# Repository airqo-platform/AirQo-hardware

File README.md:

# AirQo-hardware
The AirQo air quality monitoring device is an IoT connected device that provides realtime measurement of particualate matter concentrations and environmental readings (atmospheric pressure, relative humidity and temperature). The device is powered by a Li-ion battery and connects to the internet over a 2G GSM network.
## Folder Structure
- [**Firmware**](./firmware)
    - Contains the various firmware projects for AirQo hardware, specific to different build environments.
- [**Hardware**](./hardware)
    - Contains the hardware designs for AirQo hardware, 3d models for 3d printing, Schematic and PCB designs.
- [**docs**](./docs)
    - Contains relevant documentation and templates.
## Hardware design
The device is currently designed around an [Atmega2560](https://ww1.microchip.com/downloads/aemDocuments/documents/OTH/ProductDocuments/DataSheets/ATmega640-1280-1281-2560-2561-Datasheet-DS40002211A.pdf) microcontroller, that hosts the device firmware.
### block diagram 

### Sensors
* Particulate matter sensors [Plantower Pms5003]()

* Environmental sensors     [BME280](),[SHT25]()

* GPS                        [NEO6-GPS-module]()

* Communication              [Sim800l-GSM-GPRS]()

### CAD tools
List of tools used to design the AirQo monitor
PCB tools, 3d tools, links to design files here on github

## Firmware design
### Developed with cpp and arduino framework
The firmware provides the AirQo monitor with a number of features
* Realtime measurements of particulate matter concentrations
* Logging of data to local storage
* Over The Air Firmware Updates (OTA)
## License
This project is licensed under the MIT License - see the [LICENSE.md](LICENSE.md) file for details

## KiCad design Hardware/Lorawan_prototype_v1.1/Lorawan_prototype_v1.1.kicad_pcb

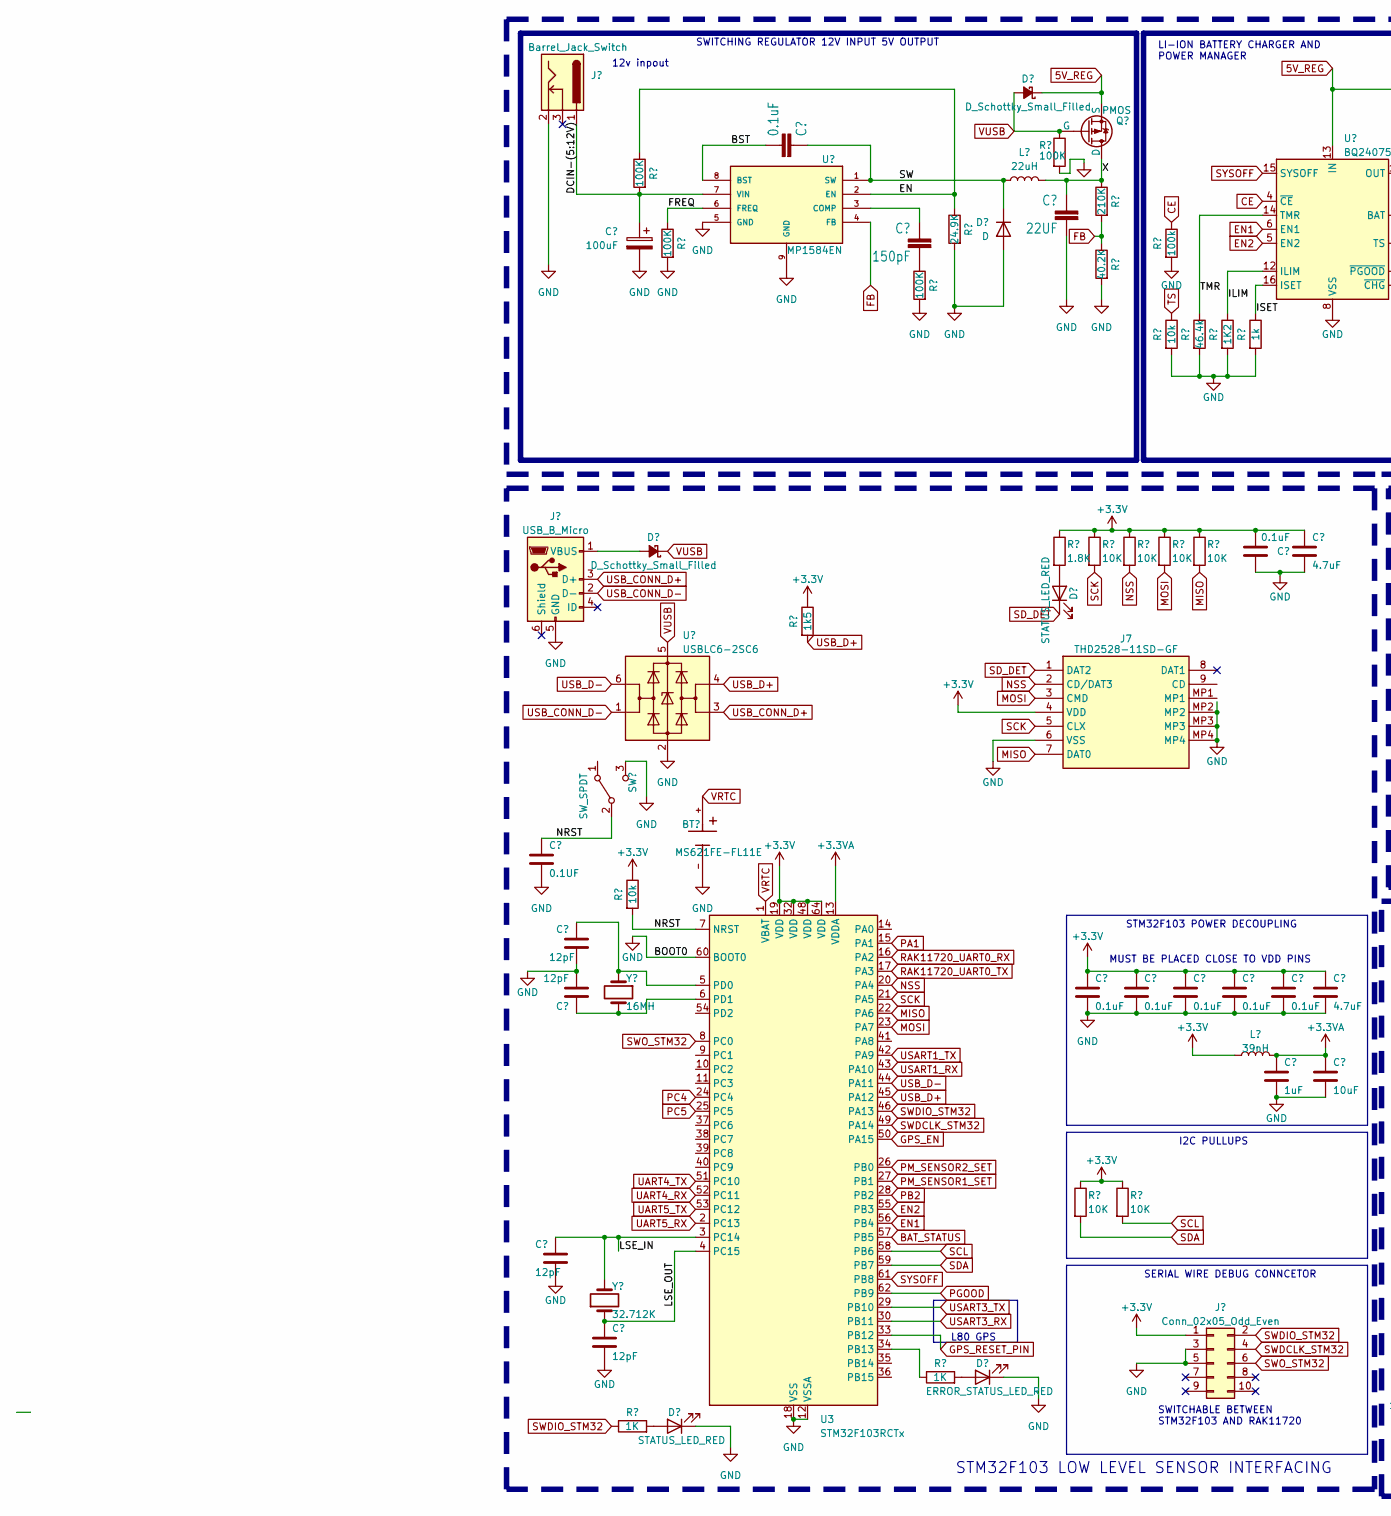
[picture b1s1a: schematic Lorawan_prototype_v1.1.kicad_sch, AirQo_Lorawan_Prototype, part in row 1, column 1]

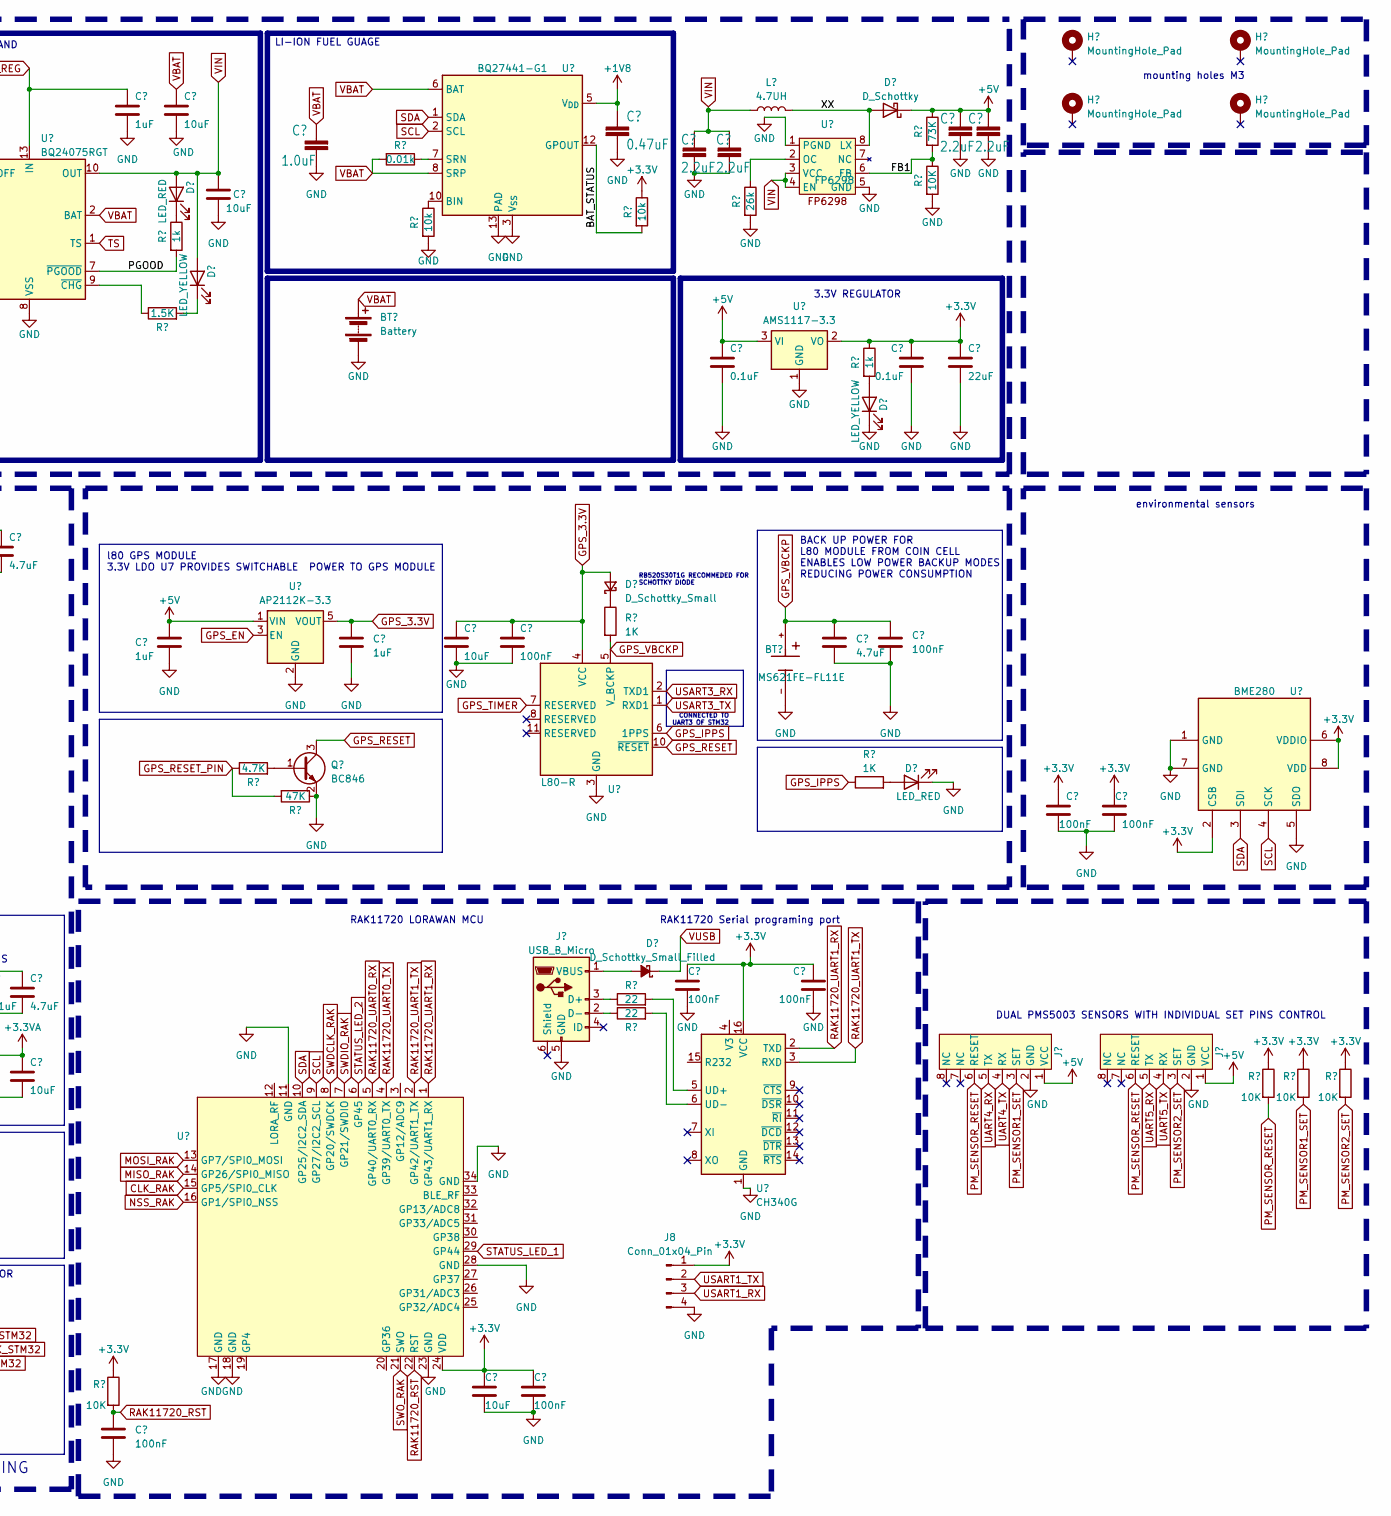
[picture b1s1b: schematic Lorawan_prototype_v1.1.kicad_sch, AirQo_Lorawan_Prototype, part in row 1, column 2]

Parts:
BT1, BT3: MS621FE-FL11E; BAT_MS621FE-FL11E; PARTREV E
BT2: Battery; BatteryHolder_Keystone_1042_1x18650
C1: 0.1UF; C_0603_1608Metric
C2, C3, C4, C5: 12pF; C_0603_1608Metric
C6: 100uF; CP_Radial_D7.5mm_P2.50mm
C7, C10, C11, C12, C13, C15, C32, C37, C43: 0.1uF; C_0603_1608Metric
C8: 150pF; C_0603_1608Metric
C9: 22UF; C_0805_2012Metric
C14, C19, C20, C24: 1uF; C_0603_1608Metric
C16, C35, C44: 4.7uF; C_0805_2012Metric
C17, C21, C22, C25, C26: 10uF; C_0805_2012Metric
C18, C27, C28, C30, C34, C36, C41, C42: 100nF; C_0603_1608Metric
C23: 1.0uF; C_0603_1608Metric
C29: 0.47uF; C_0603_1608Metric
C31, C33, C38, C40: 2.2uF; C_0603_1608Metric
C39: 22uF; C_0603_1608Metric
D1, D8: D_Schottky_Small_Filled; D_0603_1608Metric_Pad1.05x0.95mm_HandSolder
D2, D12: STATUS_LED_RED; LED_0603_1608Metric
D3: D; DIOM4336X265N
D4: D_Schottky_Small_Filled; DIOM4336X265N
D5, D11: LED_RED; LED_0603_1608Metric
D6, D9: LED_YELLOW; LED_0603_1608Metric
D7: D_Schottky_Small; D_1206_3216Metric
D10: D_Schottky; DIOM4336X265N
D13: ERROR_STATUS_LED_RED; LED_0603_1608Metric
H1, H2, H3, H4: MountingHole_Pad; MountingHole_3mm_Pad_Via
J1, J4: USB_B_Micro; USB_Micro-B_GCT_USB3076-30-A
J2: Barrel_Jack_Switch; BarrelJack_CUI_PJ-063AH_Horizontal
J3: Conn_02x05_Odd_Even; IDC-Header_2x05_P2.54mm_Vertical
J5, J6: Molex_CLIK-Mate_502382-0870_1x08-1MP_P1.25mm_Vertical
J7: THD2528-11SD-GF; THD252811SDGF; Manufacturer_Part_Number THD2528-11SD-GF
J8: Conn_01x04_Pin; PinHeader_1x04_P2.54mm_Vertical
L1: 22uH; L_7.3x7.3_H4.5
L2: 39nH; L_0603_1608Metric
L3: 4.7UH; L_7.3x7.3_H4.5
Q1: PMOS; TO-252-2
Q2: BC846; SOT-23
R1: 10k; R_0603_1608Metric_Pad0.98x0.95mm_HandSolder
R2, R23, R28, R42: 1K; R_0603_1608Metric
R3, R4, R6, R8: 100K; R_0603_1608Metric
R5: 1k5; R_0603_1608Metric_Pad0.98x0.95mm_HandSolder
R7: 24.9K; R_0603_1608Metric
R9, R12, R17, R30, R31, R32, R33, R37, R38, R39, R40: 10K; R_0603_1608Metric
R10: 210K; R_0603_1608Metric
R11: 40.2K; R_0603_1608Metric
R13, R34, R35: 10k; R_0603_1608Metric
R14: 46.4k; R_0603_1608Metric
R15: 1K2; R_0603_1608Metric
R16, R19, R27: 1k; R_0603_1608Metric
R18: 1.5K; R_0603_1608Metric
R20: 4.7K; R_0603_1608Metric
R21: 47K; R_0603_1608Metric
R22: 0.01k; R_0603_1608Metric
R24, R25: 22; R_0603_1608Metric_Pad0.98x0.95mm_HandSolder
R26: 26k; R_0603_1608Metric
R29: 73K; R_0603_1608Metric
R36: 1.8K; R_0603_1608Metric
R41: 100k; R_0603_1608Metric
SW1: SW_SPDT; SW_SPST_PTS645
U1: USBLC6-2SC6; SOT-23-6
U2: MP1584EN; SOIC127P600X170-9N
U3: STM32F103RCTx; LQFP-64_10x10mm_P0.5mm
U4: BQ24075RGT; VQFN-16-1EP_3x3mm_P0.5mm_EP1.6x1.6mm
U5: AP2112K-3.3; SOT-23-5
U6: RAK3172
U7: BQ27441-G1; Texas_S-PDSO-N12
U8: L80-R; Quectel_L80-R
U9: CH340G; SOIC-16_3.9x9.9mm_P1.27mm
U10: AMS1117-3.3; SOT-223-3_TabPin2
U11: FP6298; SOIC127P599X175-9N
U12: BME280; Bosch_LGA-8_2.5x2.5mm_P0.65mm_ClockwisePinNumbering
Y1: 32.712K; Crystal_C38-LF_D3.0mm_L8.0mm_Horizontal
Y2: 16MH; Crystal_HC52-6mm_Vertical

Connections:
5V_REG: C19.1, D4.1 (K), Q1.3 (S), U4.13 (IN)
+1V8: C29.1, U7.5 (V_{DD})
+3.3V: C10.1, C11.1, C12.1, C13.1, C15.1, C16.1, C26.1, C28.1, C30.1, C34.1, C37.1, C39.1, C41.1, C42.1, C43.2, C44.1, J3.1, J7.4 (VDD), J8.1, L2.1, R1.1, R5.1, R9.1, R12.1, R17.1, R27.1, R31.1, R32.1, R33.1, R35.1, R36.1, R37.1, R38.1, R39.1, R40.1, U3.19 (VDD), U3.32 (VDD), U3.48 (VDD), U3.64 (VDD), U6.24 (VDD), U9.16 (VCC), U10.2 (VO), U12.2 (CSB), U12.6 (VDDIO), U12.8 (VDD); also elsewhere on the board
+3.3VA: C14.1, C17.1, L2.2, U3.13 (VDDA)
+5V: C20.1, C32.1, C38.1, C40.1, D10.1 (K), J5.1 (VCC), J6.1 (VCC), R29.1, U5.1 (VIN), U10.3 (VI)
/BST: C7.2, U2.8 (BST)
/DCIN-(5:12V): C6.1, J2.1, R3.2, U2.7 (VIN)
/EN: R3.1, R7.1, U2.2 (EN)
/FB1: R29.2, R30.1, U11.6 (FB)
/FREQ: R4.1, U2.6 (FREQ)
/ILIM: R15.1, U4.12 (ILIM)
/ISET: R16.1, U4.16 (ISET)
/LSE_IN: C2.1, U3.3 (PC14), Y1.2
/LSE_OUT: C5.1, U3.4 (PC15), Y1.1
/NRST: C1.1, R1.2, SW1.2 (B), U3.7 (NRST)
/SW: C7.1, D3.1 (K), L1.2, U2.1 (SW)
/TMR: R14.1, U4.14 (TMR)
/X: C9.1, L1.1, Q1.1 (D), R10.1
/XX: D10.2 (A), L3.2, U11.8 (LX)
BAT_STATUS: R35.2, U3.57 (PB5), U7.12 (GPOUT)
CE: R41.1, U4.4 (~CE)
CLK_RAK: U6.15 (GP5/SPI0_CLK)
EN1: U3.56 (PB4), U4.6 (EN1)
EN2: U3.55 (PB3), U4.5 (EN2)
FB: R10.2, R11.1, U2.4 (FB)
GND: BT1.-, BT2.2 (-), BT3.-, C1.2, C2.2, C3.2, C4.2, C5.2, C6.2, C9.2, C10.2, C11.2, C12.2, C13.2, C14.2, C15.2, C16.2, C17.2, C18.2, C19.2, C20.2, C21.2, C22.2, C23.2, C24.2, C25.2, C26.2, C27.2, C28.2, C29.2, C30.2, C31.2, C32.2, C33.2, C34.2, C35.2, C36.1, C37.2, C38.2, C39.2, C40.2, C41.2, C42.2, C43.1, C44.2, D2.1 (K), D3.2 (A), D9.1 (K), D11.1 (K), D13.1 (K), J1.5 (GND), J2.2, J3.3, J3.5, J4.5 (GND), J5.2 (GND), J6.2 (GND), J7.6 (VSS), J7.MP2, J7.MP3, J7.MP4, J8.4, Q2.2 (E), R4.2, R6.2, R7.2, R8.2, R11.2, R13.2, R14.2, R15.2, R16.2, R21.1, R26.2, R30.2, R34.2, R41.2, SW1.3 (C), U1.2 (GND), U2.5 (GND), U2.9 (GND), U3.12 (VSSA), U3.18 (VSS), U3.31 (VSS), U3.47 (VSS), U3.60 (BOOT0), U3.63 (VSS), U4.8 (VSS), U4.17 (VSS), U5.2 (GND), U6.11 (GND), U6.17 (GND), U6.18 (GND), U6.23 (GND), U6.28 (GND), U6.34 (GND), U7.3 (V_{SS}), U7.13 (PAD), U8.3 (GND), U8.12 (GND), U9.1 (GND), U10.1 (GND), U11.1 (PGND), U11.5 (GND), U12.1 (GND), U12.5 (SDO), U12.7 (GND); also elsewhere on the board
GPS_3.3V: C24.1, C25.1, C27.1, D7.2 (A), U5.5 (VOUT), U8.4 (VCC)
GPS_EN: U3.50 (PA15), U5.3 (EN)
GPS_IPPS: R28.1, U8.6 (1PPS)
GPS_RESET: Q2.3 (C), U8.10 (~RESET)
GPS_RESET_PIN: R20.1, R21.2, U3.33 (PB12)
GPS_TIMER: U8.7 (RESERVED)
GPS_VBCKP: BT3.+, C35.1, C36.2, R23.2, U8.5 (V_BCKP)
MISO: J7.7 (DAT0), R40.2, U3.22 (PA6)
MISO_RAK: U6.14 (GP26/SPI0_MISO)
MOSI: J7.3 (CMD), R39.2, U3.23 (PA7)
MOSI_RAK: U6.13 (GP7/SPI0_MOSI)
NSS: J7.2 (CD/DAT3), R38.2, U3.20 (PA4)
NSS_RAK: U6.16 (GP1/SPI0_NSS)
unnamed: C8.2, R6.1
unnamed: D1.2 (A), J1.1 (VBUS)
unnamed: D2.2 (A), R2.2
unnamed: D5.1 (K), R19.1
unnamed: D6.1 (K), R18.2
unnamed: D7.1 (K), R23.1
unnamed: D8.2 (A), J4.1 (VBUS)
unnamed: D9.2 (A), R27.2
unnamed: D11.2 (A), R28.2
unnamed: D12.2 (A), R36.2
unnamed: D13.2 (A), R42.2
unnamed: J4.3 (D+), R24.1
unnamed: J4.2 (D-), R25.1
unnamed: Q2.1 (B), R20.2
unnamed: C8.1, U2.3 (COMP)
unnamed: R42.1, U3.34 (PB13)
unnamed: C3.1, U3.5 (PD0), Y2.1
unnamed: C4.1, U3.6 (PD1), Y2.2
unnamed: R18.1, U4.9 (~CHG)
unnamed: R34.1, U7.10 (BIN)
unnamed: R22.1, U7.7 (SRN)
unnamed: R24.2, U9.5 (UD+)
unnamed: R25.2, U9.6 (UD-)
unnamed: R26.1, U11.2 (OC)
PA1: U3.15 (PA1)
PB2: U3.28 (PB2)
PC4: U3.24 (PC4)
PC5: U3.25 (PC5)
PGOOD: R19.2, U3.62 (PB9), U4.7 (~PGOOD)
PM_SENSOR1_SET: J5.3 (SET), R32.2, U3.27 (PB1)
PM_SENSOR2_SET: J6.3 (SET), R33.2, U3.26 (PB0)
PM_SENSOR_RESET: J5.6 (RESET), J6.6 (RESET), R31.2
RAK11720_RST: C18.1, R17.2, U6.22 (RST)
RAK11720_UART0_RX: U3.16 (PA2), U6.5 (GP40/UART0_RX)
RAK11720_UART0_TX: U3.17 (PA3), U6.4 (GP39/UART0_TX)
RAK11720_UART1_RX: U6.1 (GP43/UART1_RX), U9.2 (TXD)
RAK11720_UART1_TX: U6.2 (GP42/UART1_TX), U9.3 (RXD)
SCK: J7.5 (CLX), R37.2, U3.21 (PA5)
SD_DET: D12.1 (K), J7.1 (DAT2)
STATUS_LED_1: U6.29 (GP44)
STATUS_LED_2: U6.6 (GP45)
SWDCLK_RAK: U6.8 (GP20/SWDCK)
SWDCLK_STM32: J3.4, U3.49 (PA14)
SWDIO_RAK: U6.7 (GP21/SWDIO)
SWDIO_STM32: J3.2, R2.1, U3.46 (PA13)
SWO_RAK: U6.21 (SWO)
SWO_STM32: J3.6, U3.8 (PC0)
SYSOFF: U3.61 (PB8), U4.15 (SYSOFF)
TS: R13.1, U4.1 (TS)
UART4_RX: J5.5 (TX), U3.52 (PC11)
UART4_TX: J5.4 (RX), U3.51 (PC10)
UART5_RX: J6.5 (TX), U3.2 (PC13)
UART5_TX: J6.4 (RX), U3.53 (PC12)
USART3_RX: U3.30 (PB11), U8.2 (TXD1)
USART3_TX: U3.29 (PB10), U8.1 (RXD1)
USB_CONN_D+: J1.3 (D+), U1.3 (I/O2)
USB_CONN_D-: J1.2 (D-), U1.1 (I/O1)
USB_D+: R5.2, U1.4 (I/O2), U3.45 (PA12)
USB_D-: U1.6 (I/O1), U3.44 (PA11)
VBAT: BT2.1 (+), C21.1, C23.1, R22.2, U4.2 (BAT), U4.3 (BAT), U7.6 (BAT), U7.8 (SRP)
VIN: C22.1, C31.1, C33.1, D5.2 (A), D6.2 (A), L3.1, U4.10 (OUT), U4.11 (OUT), U11.3 (VCC), U11.4 (EN)
VRTC: BT1.+, U3.1 (VBAT)
VUSB: D1.1 (K), D4.2 (A), D8.1 (K), Q1.2 (G), R8.1, U1.5 (VBUS)

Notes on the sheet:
SWITCHABLE BETWEEN STM32F103 AND RAK11720
LI-ION BATTERY CHARGER AND POWER MANAGER
BACK UP POWER FOR L80 MODULE FROM COIN CELL ENABLES LOW POWER BACKUP MODES REDUCING POWER CONSUMPTION
STM32F103 LOW LEVEL SENSOR INTERFACING
mounting holes M3
RB520S30T1G RECOMMEDED FOR SCHOTTKY DIODE
SERIAL WIRE DEBUG CONNCETOR
CONNECTED TO UART3 OF STM32
l80 GPS MODULE 3.3V LDO U7 PROVIDES SWITCHABLE POWER TO GPS MODULE
RAK11720 LORAWAN MCU
LI-ION FUEL GUAGE
12v inpout
3.3V REGULATOR
I2C PULLUPS
DUAL PMS5003 SENSORS WITH INDIVIDUAL SET PINS CONTROL
MUST BE PLACED CLOSE TO VDD PINS
SWITCHING REGULATOR 12V INPUT 5V OUTPUT
L80 GPS
STM32F103 POWER DECOUPLING
RAK11720 Serial programing port
environmental sensors

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
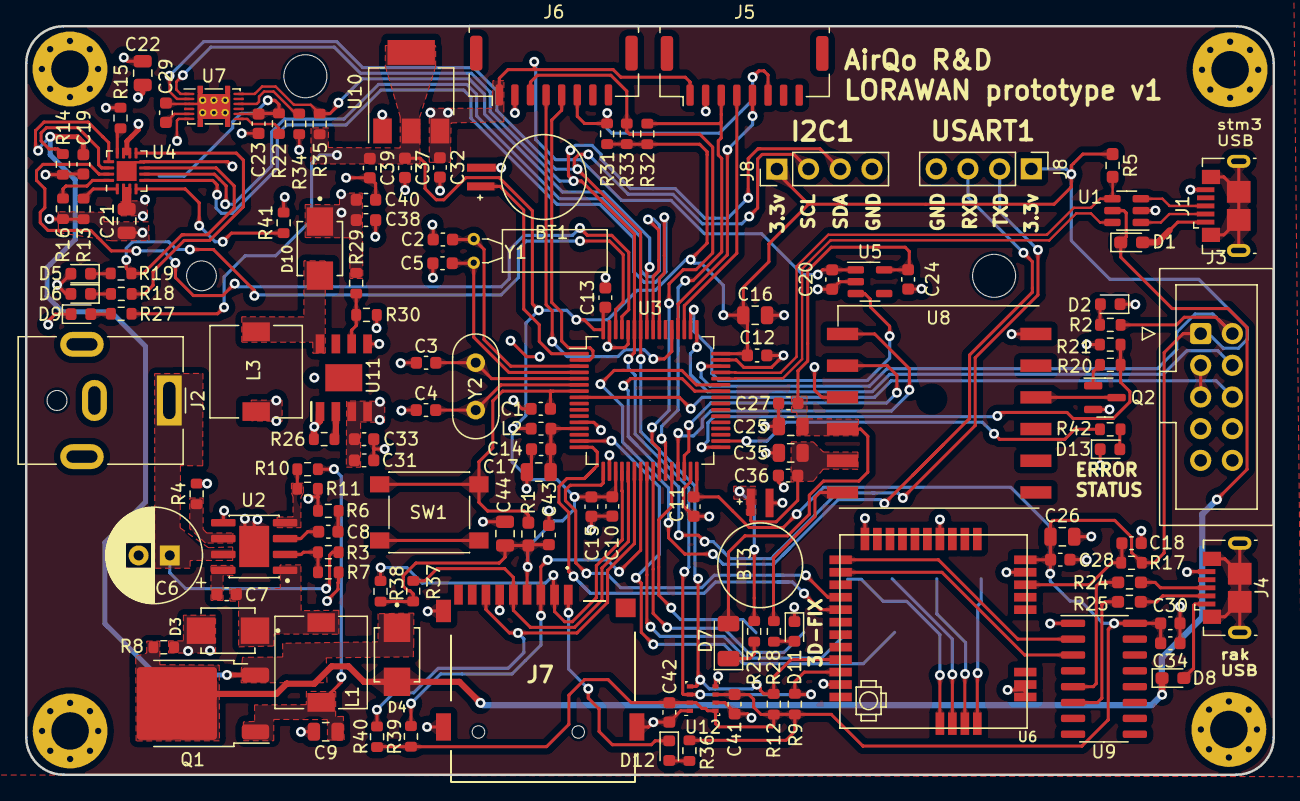
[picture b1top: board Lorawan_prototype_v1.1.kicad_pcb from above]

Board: 2 copper layers, 100.0 x 60.0 mm, 135 parts (1 on the bottom side), 92 nets.

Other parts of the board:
J8#2: Conn_01x04_Pin; PinHeader_1x04_P2.54mm_Vertical

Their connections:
+3.3V: J8#2.1; also elsewhere on the board
GND: J8#2.4; also elsewhere on the board

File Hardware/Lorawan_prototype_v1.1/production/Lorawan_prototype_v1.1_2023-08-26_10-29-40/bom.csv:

Designator,Footprint,Quantity,Value,LCSC Part #
"BT1, BT3",BAT_MS621FE-FL11E,2,MS621FE-FL11E,
BT2,BatteryHolder_Keystone_1042_1x18650,1,Battery,
"C1, C10, C11, C12, C13, C15, C32, C37, C43, C7",0603,10,0.1UF,
"C14, C19, C20, C24",0603,4,1uF,
"C16, C35, C44",0805,3,4.7uF,
"C17, C21, C22, C25, C26",0805,5,10uF,
"C18, C27, C28, C30, C34, C36, C41, C42",0603,8,100nF,
"C2, C3, C4, C5",0603,4,12pF,
C23,0603,1,1.0uF,
C29,0603,1,0.47uF,
"C31, C33, C38, C40",0603,4,2.2uF,
C39,0603,1,22uF,
C6,CP_Radial_D7.5mm_P2.50mm,1,100uF,
C8,0603,1,150pF,
C9,0805,1,22UF,
"D1, D8",0603,2,D_Schottky_Small_Filled,
D10,DIOM4336X265N,1,D_Schottky,
"D11, D5, D6",0603,3,LED_RED,
"D12, D2",0603,2,STATUS_LED_RED,
D3,DIOM4336X265N,1,D,
D4,DIOM4336X265N,1,D_Schottky_Small_Filled,
D7,1206,1,D_Schottky_Small,
D9,0603,1,LED_YELLOW,
"H1, H2, H3, H4",MountingHole_3mm_Pad_Via,4,MountingHole_Pad,
"J1, J4",USB_Micro-B_GCT_USB3076-30-A,2,USB_B_Micro,
J2,BarrelJack_CUI_PJ-063AH_Horizontal,1,Barrel_Jack_Switch,
J3,IDC-Header_2x05_P2.54mm_Vertical,1,Conn_02x05_Odd_Even,
"J5, J6",Molex_CLIK-Mate_502382-0870_1x08-1MP_P1.25mm_Vertical,2,~,
J7,THD252811SDGF,1,THD2528-11SD-GF,
L1,L_7.3x7.3_H4.5,1,22uH,
L2,0603,1,39nH,
L3,L_7.3x7.3_H4.5,1,4.7UH,
Q1,TO-252-2,1,PMOS,
Q2,SOT-23,1,BC846,
"R1, R12, R13, R17, R30, R31, R32, R33, R34, R35, R37, R38, R39, R40, R9",0603,15,10k,
R10,0603,1,210K,
R11,0603,1,40.2K,
R14,0603,1,46.4k,
R15,0603,1,1K2,
"R16, R19, R2, R23, R27, R28",0603,6,1k,
R18,0603,1,1.5K,
R20,0603,1,4.7K,
R21,0603,1,47K,
R22,0603,1,0.01k,
"R24, R25",0603,2,22,
R26,0603,1,26k,
R29,0603,1,73K,
"R3, R4, R6, R8",0603,4,100K,
R36,0603,1,1.8K,
R5,0603,1,1k5,
R7,0603,1,24.9K,
SW1,SW_SPST_PTS645,1,SW_SPDT,
U1,SOT-23-6,1,USBLC6-2SC6,
U10,SOT-223-3_TabPin2,1,AMS1117-3.3,
U11,SOIC127P599X175-9N,1,FP6298,
U12,Bosch_LGA-8_2.5x2.5mm_P0.65mm_ClockwisePinNumbering,1,BME280,
U2,SOIC127P600X170-9N,1,MP1584EN,
U3,LQFP-64_10x10mm_P0.5mm,1,STM32F103RCTx,
U4,VQFN-16-1EP_3x3mm_P0.5mm_EP1.6x1.6mm,1,BQ24075RGT,
U5,SOT-23-5,1,AP2112K-3.3,
U6,RAK3172,1,~,
U7,Texas_S-PDSO-N12,1,BQ27441-G1,
U8,Quectel_L80-R,1,L80-R,
U9,SOIC-16_3.9x9.9mm_P1.27mm,1,CH340G,
Y1,Crystal_C38-LF_D3.0mm_L8.0mm_Horizontal,1,32.712K,
Y2,Crystal_HC52-6mm_Vertical,1,16MH,

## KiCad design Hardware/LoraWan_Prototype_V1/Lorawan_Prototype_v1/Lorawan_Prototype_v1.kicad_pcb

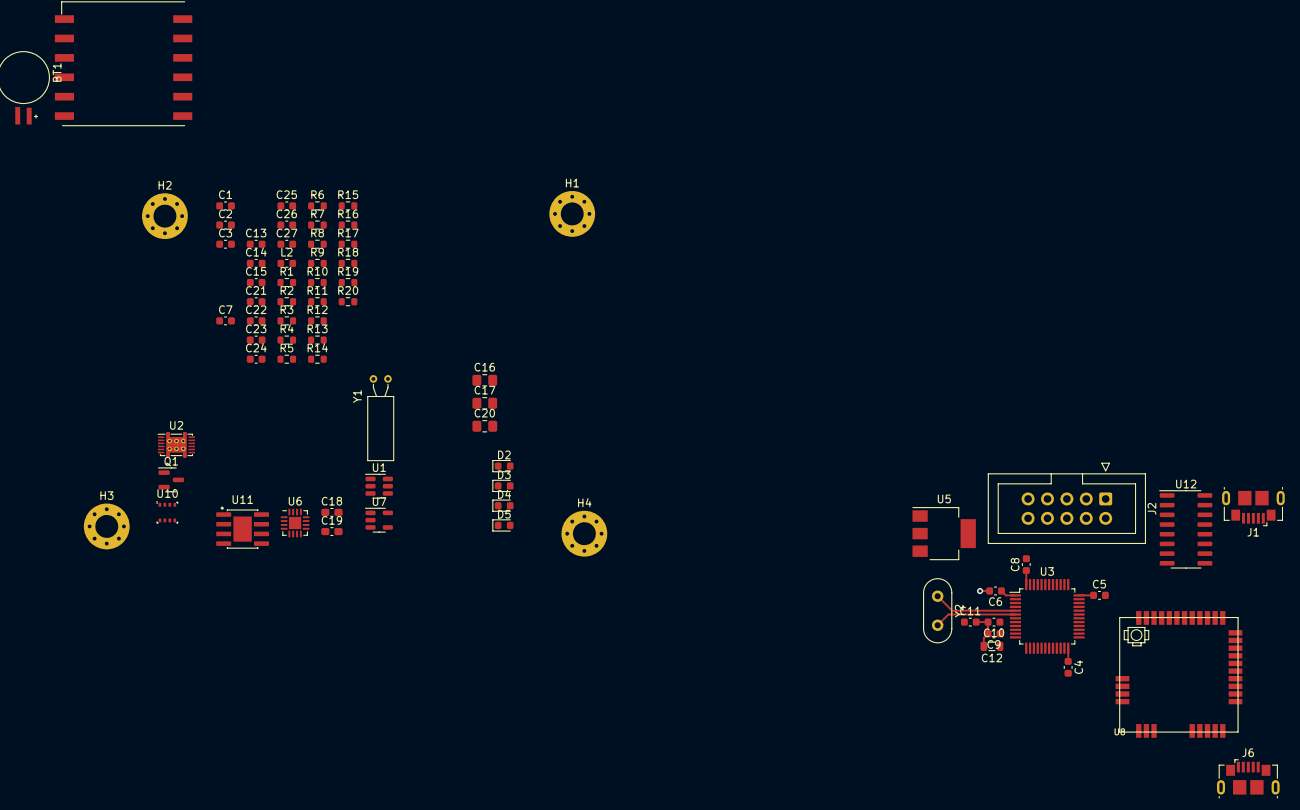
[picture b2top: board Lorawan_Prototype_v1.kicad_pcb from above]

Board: 2 copper layers, 74 parts (0 on the bottom side), 48 nets.

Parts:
BT1: MS621FE-FL11E; BAT_MS621FE-FL11E
C1: 1.0uF; C_0603_1608Metric
C2: 0.47uF; C_0603_1608Metric
C3, C4, C5, C6, C7, C8, C10: 0.1uF; C_0603_1608Metric
C9, C14, C15, C25: 1uF; C_0603_1608Metric
C11: 4.7uF; C_0603_1608Metric
C12: 10uF; L_0805_2012Metric
C13, C21, C22, C23: 100nF; C_0603_1608Metric
C16, C17: 10uF; C_0805_2012Metric_Pad1.18x1.45mm_HandSolder
C18, C19: 100nF; C_0603_1608Metric_Pad1.08x0.95mm_HandSolder
C20: 4.7uF; C_0805_2012Metric_Pad1.18x1.45mm_HandSolder
C24: 22uF; C_0603_1608Metric
C26, C27: 10uF; C_0603_1608Metric
D2, D4, D5: LED_RED; LED_0603_1608Metric
D3: LED_YELLOW; LED_0603_1608Metric
H1, H2, H3, H4: MountingHole_Pad; MountingHole_3mm_Pad_Via
J1, J6: USB_B_Micro; USB_Micro-B_GCT_USB3076-30-A
J2: Conn_02x05_Odd_Even; IDC-Header_2x05_P2.54mm_Vertical
L2: L; L_0603_1608Metric
Q1: BC846; SOT-23
R1: 0.01k; R_0603_1608Metric
R2, R20: 10k; R_0603_1608Metric
R3, R15, R17, R18, R19: 1k; R_0603_1608Metric
R4, R5, R6, R11, R12, R13: 10K; R_0603_1608Metric
R7: 4.7K; R_0603_1608Metric
R8: 47K; R_0603_1608Metric
R9, R10: 1K; R_0603_1608Metric
R14: 200K; R_0603_1608Metric
R16: 1.5K; R_0603_1608Metric
U1: USBLC6-2SC6; SOT-23-6
U2: BQ27441-G1; Texas_S-PDSO-N12
U3: STM32F103CBT6; LQFP-48_7x7mm_P0.5mm
U5: AMS1117-3.3; SOT-223-3_TabPin2
U6: BQ24075RGT; VQFN-16-1EP_3x3mm_P0.5mm_EP1.6x1.6mm
U7: AP2112K-3.3; SOT-23-5
U8: RAK3172
U9: L80-R; Quectel_L80-R
U10: BME280; Bosch_LGA-8_2.5x2.5mm_P0.65mm_ClockwisePinNumbering
U11: MP1584EN; SOIC127P600X170-9N
U12: CH340G; SOIC-16_3.9x9.9mm_P1.27mm
Y1: 32.712K; Crystal_C38-LF_D3.0mm_L8.0mm_Horizontal
Y2: 16MH; Crystal_HC52-6mm_Vertical

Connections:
+1V8: C2.1, U2.5 (V_{DD})
+3.3V: C4.1, C5.1, C6.1, C7.1, C8.1, C10.1, C11.1, C17.1, C19.1, C22.1, C23.1, C24.1, J2.1, L2.2, R4.1, R5.1, R6.1, R11.1, R12.1, R13.1, U3.1 (VBAT), U3.24 (VDD), U3.36 (VDD), U3.48 (VDD), U8.24 (VDD), U10.2 (CSB), U10.6 (VDDIO), U10.8 (VDD)
+3.3VA: C9.1, C12.1, U3.9 (VDDA)
+5V: C25.1, J1.1 (VBUS), U1.5 (VBUS), U6.13 (IN)
/BOOT0: R2.1, U3.44 (BOOT0)
/ILIM: R18.1, U6.12 (ILIM)
/ISET: R17.1, U6.16 (ISET)
/TMR: R19.1, U6.14 (TMR)
EN1: U3.41 (PB5), U6.6 (EN1)
EN2: U3.42 (PB6), U6.5 (EN2)
GND: BT1.-, C1.2, C2.2, C3.2, C4.2, C5.2, C6.2, C7.2, C8.2, C9.2, C10.2, C11.2, C12.2, C13.2, C14.2, C15.2, C16.2, C17.2, C18.2, C19.2, C20.2, C21.2, C22.2, C23.2, C24.2, C25.2, C26.2, C27.2, D2.1 (K), D3.1 (K), J1.5 (GND), J2.3, J2.5, Q1.2 (E), R8.1, R14.2, R17.2, R18.2, R19.2, R20.2, U1.2 (GND), U2.3 (V_{SS}), U2.13 (PAD), U3.8 (VSSA), U3.23 (VSS), U3.35 (VSS), U3.47 (VSS), U5.1 (GND), U6.8 (VSS), U6.17 (VSS), U7.2 (GND), U8.11 (GND), U8.17 (GND), U8.18 (GND), U8.23 (GND), U8.28 (GND), U8.34 (GND), U9.3 (GND), U9.12 (GND), U10.1 (GND), U10.5 (SDO), U10.7 (GND), U11.5 (GND), U11.9 (GND), U12.1 (GND)
GPS_3.3V: C15.1, C16.1, C18.1, U7.5 (VOUT), U9.4 (VCC)
GPS_EN: U3.20 (PB2), U7.3 (EN)
GPS_IPPS: R10.1, U9.6 (1PPS)
GPS_RESET: Q1.3 (C), U9.10 (~RESET)
GPS_RESET_PIN: R7.1, R8.2, U3.19 (PB1)
GPS_VBCKP: BT1.+, C20.1, C21.1, R9.2, U9.5 (V_BCKP)
HSE_IN: U3.5 (PD0), Y2.1
HSE_OUT: U3.6 (PD1), Y2.2
LSE_IN: U3.2 (PC13), Y1.2
LSE_OUT: U3.3 (PC14), Y1.1
unnamed: D2.2 (A), R10.2
unnamed: D3.2 (A), R3.2
unnamed: D4.1 (K), R15.1
unnamed: D5.1 (K), R16.2
unnamed: Q1.1 (B), R7.2
unnamed: R1.1, U2.7 (SRN)
unnamed: L2.1, R3.1, U5.2 (VO)
unnamed: R16.1, U6.9 (~CHG)
unnamed: R14.1, U11.6 (FREQ)
PGOOD: R15.2, U3.38 (PA15), U6.7 (~PGOOD)
PM_SENSOR1_SET: R12.2, U3.11 (PA1)
PM_SENSOR2_SET: R13.2, U3.10 (PA0)
RAK11720_RST: C13.1, R6.2, U8.22 (RST)
SCL: R5.2, U2.2 (SCL), U8.9 (GP27/I2C2_SCL), U10.4 (SCK)
SDA: R4.2, U2.1 (SDA), U8.10 (GP25/I2C2_SDA), U10.3 (SDI)
SWDCLK: J2.4, U3.37 (PA14)
SWDIO: J2.2, U3.34 (PA13)
SWO: J2.6, U3.39 (PB3)
TS: R20.1, U6.1 (TS)
USART3_RX: U3.22 (PB11), U9.2 (TXD1)
USART3_TX: U3.21 (PB10), U9.1 (RXD1)
USB_CONN_D+: J1.3 (D+), U1.3 (I/O2)
USB_CONN_D-: J1.2 (D-), U1.1 (I/O1)
USB_D+: U1.4 (I/O2), U3.33 (PA12)
USB_D-: U1.6 (I/O1), U3.32 (PA11)
VBAT: C1.1, C26.1, R1.2, U2.6 (BAT), U2.8 (SRP), U6.2 (BAT), U6.3 (BAT)
VIN: C3.1, C14.1, C27.1, D4.2 (A), D5.2 (A), U5.3 (VI), U6.10 (OUT), U6.11 (OUT), U7.1 (VIN)

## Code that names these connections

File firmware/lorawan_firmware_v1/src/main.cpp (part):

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  4...etc
}
*/
#define BATT_STATUS_PIN   PB5
#define ERROR_LED_PIN     PB13

#define SENSOR_1_SET_PIN  PB1
#define SENSOR_2_SET_PIN  PB0

#define GPS_ENABLE_PIN    PA15
#define GPS_RESET_PIN     PB12

#define CHARGER_EN1_PIN   PB4 // enable pin for usb charger modes en1
#define CHARGER_EN2_PIN   PB3 // enable pin for usb charger modes en2

#define SD_NSS_PIN        PA4
#define SEALEVELPRESSURE_HPA (1013.25)

const uint16_t BATTERY_CAPACITY=4300; //4300mAh batteries from 
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    | EN2 | EN1 | MAXIMUM INPUT CURRENT TO BATTERY CHARGER 
    | 0   | 0   | 100mA .USB100 mode
    | 0   | 1   | 500mA .USB500 mode
    | 1   | 0   | set by an external resistor from ILIM pin to GND/vss
    | 1   | 1   | standby (USB suspend mode)
    ______________________________________________________
  */
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
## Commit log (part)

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2022-05-28 new directories for hardware repo
2022-05-28 create README
    created README
2022-05-28 adding the infra directory
2022-05-28 test
2022-06-01 first commit from okedi deogratius Airqo RnD firmware implementation
2022-06-21 deleted the authentication keys
2022-06-21 add space
2022-10-17 Add files via upload
    These are the design files for Rev C enclosure. these are .3MF files that can be sliced with PRUSA SCLICER .
    Recommended print setings:
    0.2mm layer height
    prusamnet PETG
2022-11-25 Short description This is a simple firmware for testing the operation of PMS5003 sensors in the airqo Gen5 devices.
2022-11-25 Short Description firmware to test the pm sensor operation Long Description This firmware tests both pm sensors, take a user specified number of samples and averages the readings from the sensor valu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
2023-01-07 I am commiting files
2023-01-14 just adding some fake files
2023-01-15 Create chore-firmware-setup
    EEPROMSETTINGS
    how do they work exactly
2023-01-18 Just added a comment on the suggest mode of averaging
2023-01-19 making a secrets free commit for a few files
2023-01-20 making a secret free commit for the source code files for now
2023-01-21 a reorganization of the folder structure to easily guide development of hardware projects
2023-01-28 changed folder name for revC tosomething shoter and acceptable
2023-01-28 changed folder names to shoter names
2023-01-28 added .gitignore file and a dummy file to docs folder
2023-02-04 new organisation works and trials
2023-02-09 added some ingormation on the README file, to include sytling and links, work in progress
2023-02-09 eddited the sensor list
2023-02-09 eddited image markdown syntax so as to display the block diagram
2023-02-09 eddited block diagram name to blockDiagram, eleminating the space
2023-02-24 Add files via upload
    i have made changes to existing word document for contributing to AirQo-hardware Repo FEB/2023 which was assigned to me and @marvin
    changes made were creating doc based on descending order of date events . i hope you will appreciate the changes.
2023-02-25 Added folders for file organisation
2023-02-27 changes to the naming of the firmware folders made
2023-03-04 added template folder in .github to provide guidelines on contribution and feature requests
2023-05-22 created a project folder for LORAWAN project, built around the ATMEGA2560 usedd on our monitors, and a RAK11720 LORAWAN module communicating over serial connection with AT commands
2023-05-30 resolved the folder nesting
2023-06-23 added structure for PMS sensor sampling
2023-06-23 used sample count variable instead of fixed value 60
2023-07-22 created a Kicad project for Lorawan prototype work in progress
2023-07-26 added 3.3v regulator and other suppport schematics- still a work in progress
2023-07-29 categorized power sections
2023-08-24 ive had to make a few design cahnges and hence will be removing the most recent commits and update them witht he latest designs that i am confidently going with
2023-08-24 here is the updated design utilizing a 64 pin LQFP package of the stm32f103
2023-08-24 Code allowing bi-directional communication while utilizing the thingspeak mqtt broker
2023-08-26 adding a new subfolder for inventory system
2023-08-26 optimized organization of components and routes, and added an i2c expansion pinout
2023-08-28 This is the inventory system first deploy for testing
2023-08-28 optimized placement and routing of componenets
2023-09-02 Create .gitignore
    resolved that
2023-09-02 initial deploy
2023-09-09 .env edits
2023-10-28 naming _edits
2023-11-04 naming_convention for hardware
2023-11-11 complete neaming convention
2023-11-20 PR_template
2023-11-23 reorganized the folders so as to have a single hardware and firmware folder, enclosure designs have been moved to harware folder, and all firmware has been moved to firmware folder
2023-11-23 added descriptions to readme file
2023-11-23 typo edit on readme file
2023-11-23 added a PR template to guide PR's this will be updated after we discuss
2023-11-23 removed redundant folder nesting for lorawan_prototype
2023-12-02 initial lorawan firmware development
2023-12-12 addded configuration for eeprom added lorawan communcaiton to ttn server need to deal with device secret keys now
2023-12-12 added lorawan communcation functions
2025-07-25 This is the new firmware for the AirQo devices
2026-06-23 Update README.md
    Fixed a few typos, and bulleting here and there.
